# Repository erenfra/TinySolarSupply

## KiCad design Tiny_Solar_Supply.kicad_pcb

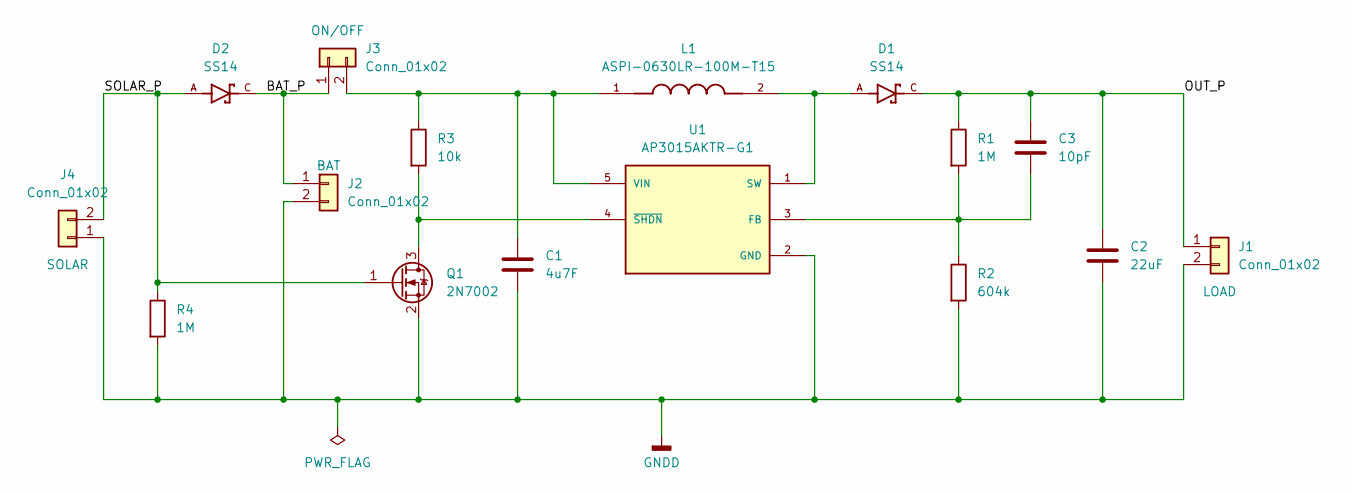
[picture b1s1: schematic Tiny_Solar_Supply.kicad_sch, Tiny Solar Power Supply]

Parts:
C1: 4u7F; C_0805_2012Metric_Pad1.18x1.45mm_HandSolder
C2: 22uF; C_1206_3216Metric_Pad1.33x1.80mm_HandSolder
C3: 10pF; C_0805_2012Metric_Pad1.18x1.45mm_HandSolder
D1, D2: SS14; DIOM4325X250N; PARTREV O2102
J1, J2, J3: Conn_01x02; PinHeader_1x02_P2.54mm_Vertical
J4: Conn_01x02; PinHeader_1x02_P2.54mm_Horizontal
L1: ASPI-0630LR-100M-T15; IND_ASPI-0630LR-100M-T15; PARTREV B
Q1: 2N7002; SOT-23
R1, R4: 1M; R_0805_2012Metric_Pad1.20x1.40mm_HandSolder
R2: 604k; R_0805_2012Metric_Pad1.20x1.40mm_HandSolder
R3: 10k; R_0805_2012Metric_Pad1.20x1.40mm_HandSolder
U1: AP3015AKTR-G1; SOT95P280X145-5N; PARTREV 1.4

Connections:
/BAT_P: D2.C, J2.1, J3.1
/OUT_P: C2.1, C3.1, D1.C, J1.1, R1.1
/SOLAR_P: D2.A, J4.2, Q1.1 (G), R4.1
GNDD: C1.2, C2.2, J1.2, J2.2, J4.1, Q1.2 (S), R2.2, R4.2, U1.2 (GND)
unnamed: C1.1, J3.2, L1.1, R3.1, U1.5 (VIN)
unnamed: Q1.3 (D), R3.2, U1.4 (~SHDN)
unnamed: C3.2, R1.2, R2.1, U1.3 (FB)
unnamed: D1.A, L1.2, U1.1 (SW)

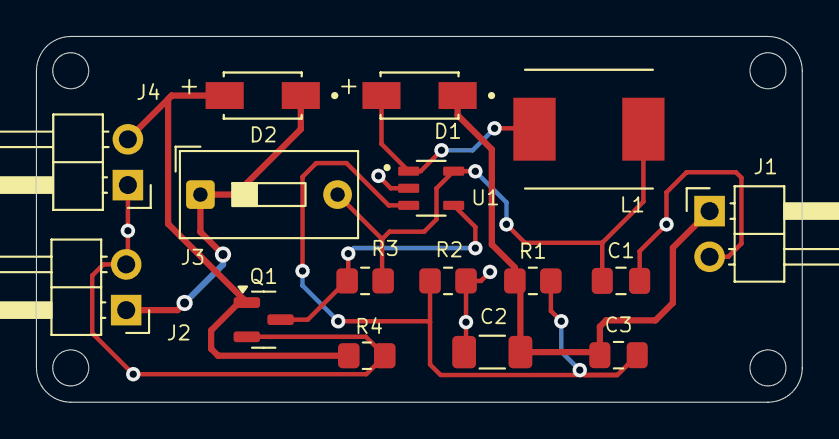
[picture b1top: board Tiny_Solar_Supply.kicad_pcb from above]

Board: 2 copper layers, 42.5 x 20.3 mm, 16 parts (0 on the bottom side), 8 nets.

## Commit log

2025-05-17 Components Placed, Annotated, Associated and Wired
2025-05-18 Schematic completed
2025-05-18 PCB completed, ready for fabrication
2025-05-18 Gerber files generated
